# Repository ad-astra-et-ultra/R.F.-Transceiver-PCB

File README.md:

# R.F.-Transceiver-PCB
### STM32 based radio-frequency transceiver PCB for IoT  applications on KiCad

## Schematic

## PCB

## 3D view

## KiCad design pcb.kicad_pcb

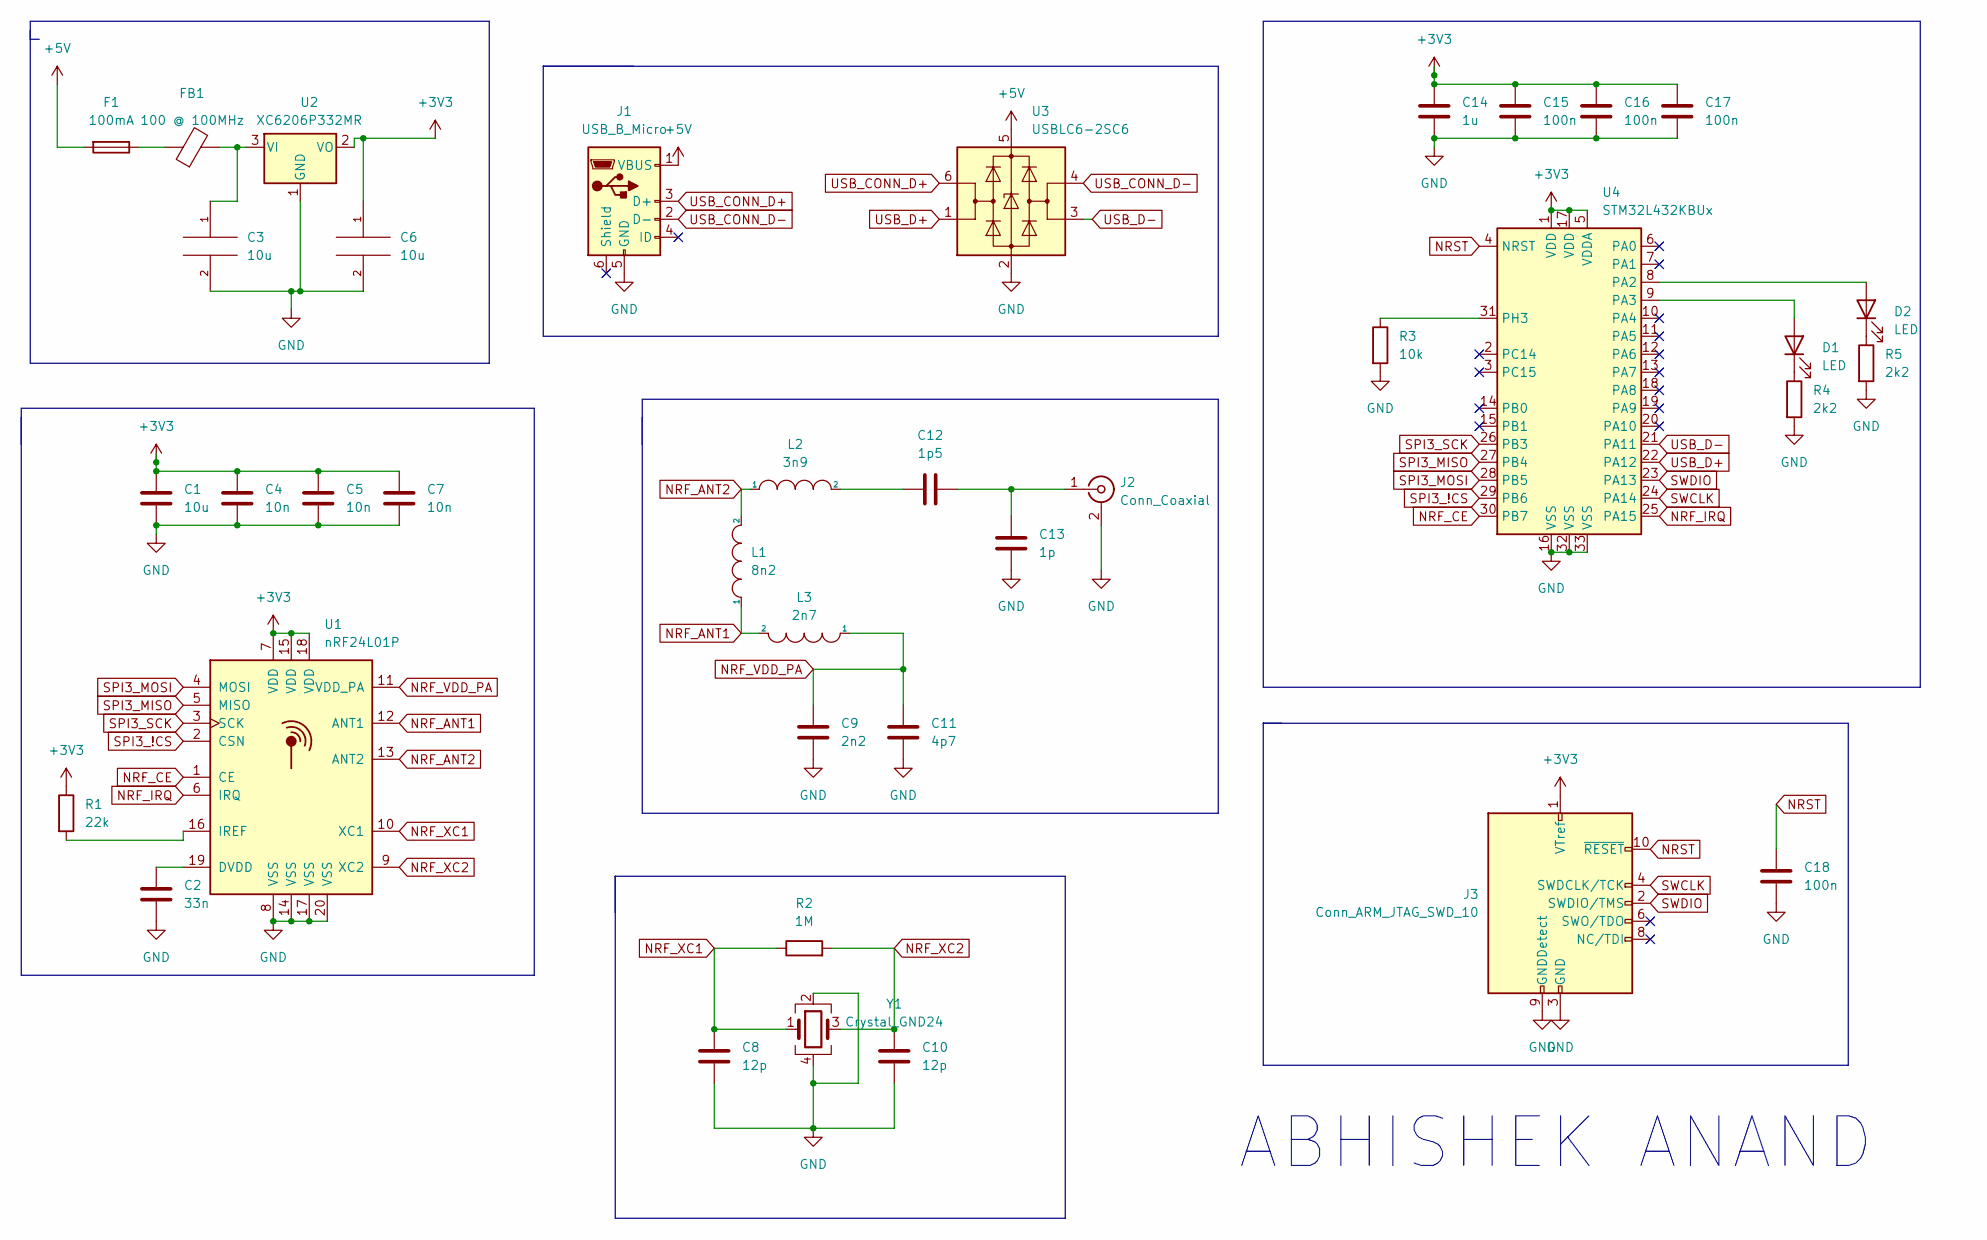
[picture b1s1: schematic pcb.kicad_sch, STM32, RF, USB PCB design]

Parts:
C1, C3, C6: 10u; C_0402_1005Metric
C2: 33n; C_0402_1005Metric
C4, C5, C7: 10n; C_0402_1005Metric
C8, C10: 12p; C_0402_1005Metric
C9: 2n2; C_0402_1005Metric
C11: 4p7; C_0402_1005Metric
C12: 1p5; C_0402_1005Metric
C13: 1p; C_0402_1005Metric
C14: 1u; C_0402_1005Metric
C15, C16, C17, C18: 100n; C_0402_1005Metric
D1, D2: LED; LED_0603_1608Metric
F1: 100mA; Fuse_1206_3216Metric
FB1: 100 @ 100MHz; L_0805_2012Metric
J1: USB_B_Micro; USB_Micro-B_Molex-105017-0001
J2: Conn_Coaxial; SMA_Samtec_SMA-J-P-X-ST-EM1_EdgeMount
J3: Conn_ARM_JTAG_SWD_10; PinHeader_2x05_P1.27mm_Vertical_SMD
L1: 8n2; L_0402_1005Metric
L2: 3n9; L_0402_1005Metric
L3: 2n7; L_0402_1005Metric
R1: 22k; R_0603_1608Metric
R2: 1M; R_0603_1608Metric
R3: 10k; R_0603_1608Metric
R4, R5: 2k2; R_0603_1608Metric
U1: nRF24L01P; QFN-20-1EP_4x4mm_P0.5mm_EP2.5x2.5mm
U2: XC6206P332MR; SOT-23
U3: USBLC6-2SC6; SOT-23-6
U4: STM32L432KBUx; QFN-32-1EP_5x5mm_P0.5mm_EP3.45x3.45mm
Y1: Crystal_GND24; Crystal_SMD_3225-4Pin_3.2x2.5mm

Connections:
+3V3: C1.1, C4.1, C5.1, C6.1, C7.1, C14.1, C15.1, C16.1, C17.1, J3.1 (VTref), R1.1, U1.7 (VDD), U1.15 (VDD), U1.18 (VDD), U2.2 (VO), U4.1 (VDD), U4.5 (VDDA), U4.17 (VDD)
+5V: F1.2, J1.1 (VBUS), U3.5 (VBUS)
GND: C1.2, C2.2, C3.2, C4.2, C5.2, C6.2, C7.2, C8.2, C9.1, C10.2, C11.1, C13.1, C14.2, C15.2, C16.2, C17.2, C18.2, J1.5 (GND), J2.2 (Ext), J3.3 (GND), J3.5 (GND), J3.9 (GNDDetect), R3.2, R4.2, R5.2, U1.8 (VSS), U1.14 (VSS), U1.17 (VSS), U1.20 (VSS), U2.1 (GND), U3.2 (GND), U4.16 (VSS), U4.32 (VSS), U4.33 (VSS), Y1.2, Y1.4
NRF_ANT1: L1.1, L3.2, U1.12 (ANT1)
NRF_ANT2: L1.2, L2.1, U1.13 (ANT2)
NRF_CE: U1.1 (CE), U4.30 (PB7)
NRF_IRQ: U1.6 (IRQ), U4.25 (PA15)
NRF_VDD_PA: C9.2, C11.2, L3.1, U1.11 (VDD_PA)
NRF_XC1: C8.1, R2.1, U1.10 (XC1), Y1.1
NRF_XC2: C10.1, R2.2, U1.9 (XC2), Y1.3
NRST: C18.1, J3.10 (~RESET), U4.4 (NRST)
unnamed: C2.1, U1.19 (DVDD)
unnamed: C12.1, L2.2
unnamed: C12.2, C13.2, J2.1 (In)
unnamed: D1.1 (K), R4.1
unnamed: D1.2 (A), U4.9 (PA3)
unnamed: D2.1 (K), R5.1
unnamed: D2.2 (A), U4.8 (PA2)
unnamed: F1.1, FB1.1
unnamed: C3.1, FB1.2, U2.3 (VI)
unnamed: R1.2, U1.16 (IREF)
unnamed: R3.1, U4.31 (PH3)
SPI3_!CS: U1.2 (CSN), U4.29 (PB6)
SPI3_MISO: U1.5 (MISO), U4.27 (PB4)
SPI3_MOSI: U1.4 (MOSI), U4.28 (PB5)
SPI3_SCK: U1.3 (SCK), U4.26 (PB3)
SWCLK: J3.4 (SWDCLK/TCK), U4.24 (PA14)
SWDIO: J3.2 (SWDIO/TMS), U4.23 (PA13)
USB_CONN_D+: J1.3 (D+), U3.6 (I/O1)
USB_CONN_D-: J1.2 (D-), U3.4 (I/O2)
USB_D+: U3.1 (I/O1), U4.22 (PA12)
USB_D-: U3.3 (I/O2), U4.21 (PA11)

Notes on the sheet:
ABHISHEK ANAND

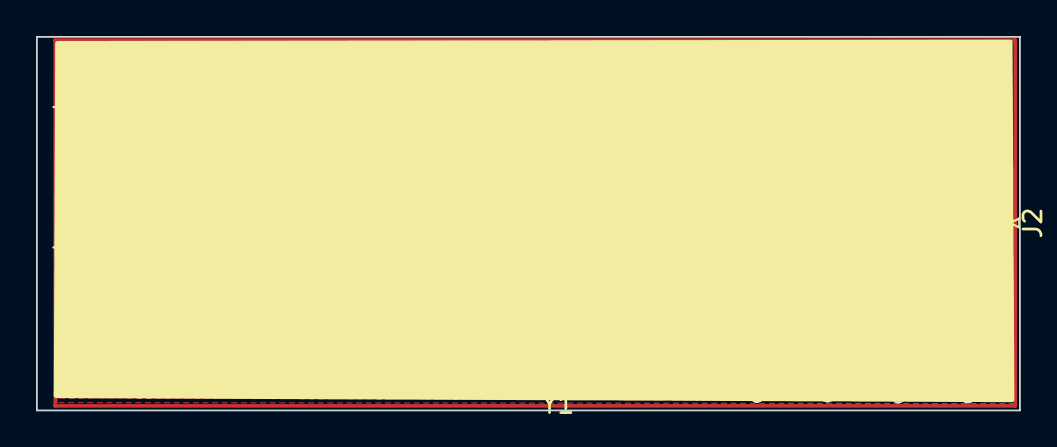
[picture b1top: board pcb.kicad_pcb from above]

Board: 4 copper layers, 54.6 x 20.8 mm, 38 parts (0 on the bottom side), 32 nets.
